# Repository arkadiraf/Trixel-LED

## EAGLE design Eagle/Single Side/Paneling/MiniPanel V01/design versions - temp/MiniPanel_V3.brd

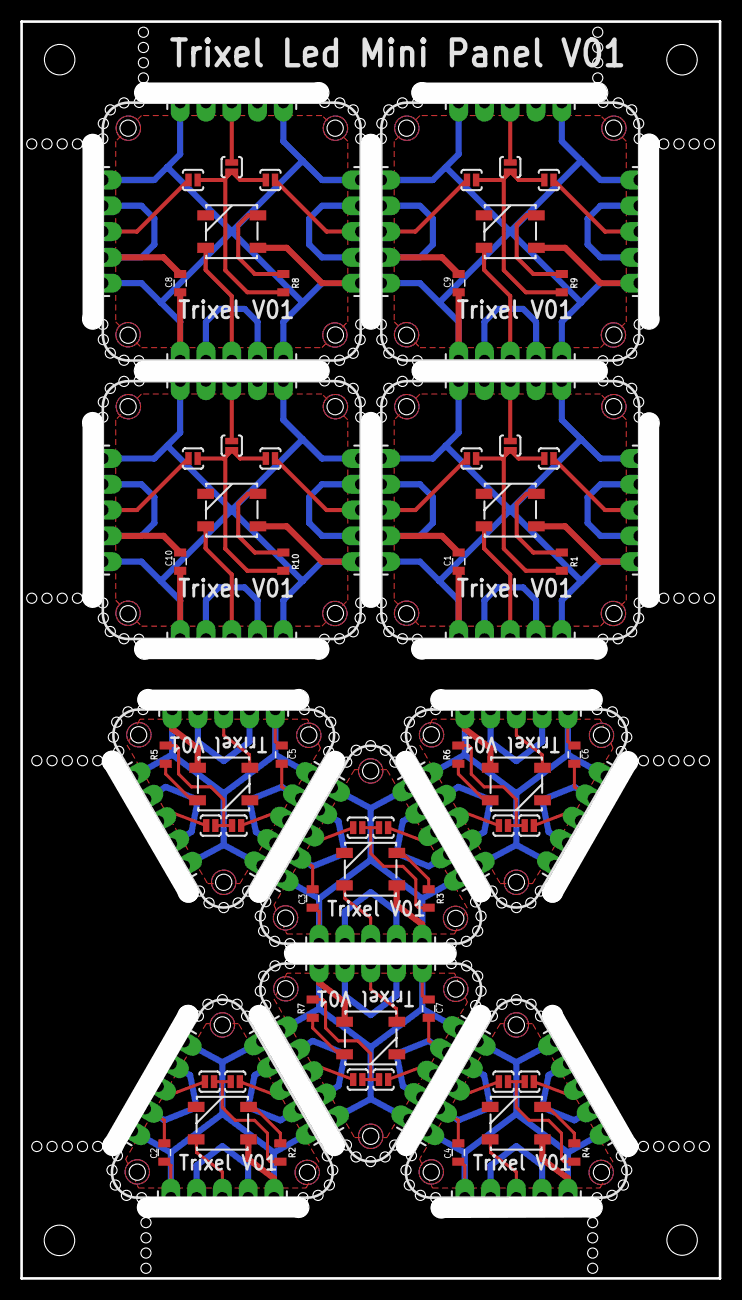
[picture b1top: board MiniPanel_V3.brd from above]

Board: 2 copper layers, 68.8 x 123.8 mm, 88 parts (0 on the bottom side), 74 nets.

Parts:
C1, C2, C3, C4, C5, C6, C7, C8, C9, C10: 0.1uF; 0805
D1, D2, D3, D4, D5, D6, D7, D8, D9, D10: WS2812B
J1, J2, J3, J4, J5, J6, J7, J8, J9, J10, J11, J12, J13, J14, J15, J16, J17, J18, J19, J20, J21, J22, J23, J24, J25, J26, J27, J28, J29, J30, J31, J32, J33, J34: 1X05_LONGPADS
JP1, JP2, JP3, JP4, JP5, JP6, JP7, JP8, JP9, JP10, JP11, JP12, JP13, JP14, JP15, JP16, JP17, JP18, JP19, JP20, JP21, JP22, JP23, JP24: JUMPER-PAD-2-NOYES_SILK; PAD-JUMPER-2-NO_YES_SILK
R1, R8, R9, R10: 0805
R2, R3, R4, R5, R6, R7: 1k; 0805

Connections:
DIN: D1.4, J22.3
DIN1: D2.4, J3.3
DIN2: D3.4, J7.3
DIN3: D4.4, J10.3
DIN4: D5.4, J13.3
DIN5: D6.4, J16.3
DIN6: D7.4, J19.3
DIN7: D8.4, J26.3
DIN8: D9.4, J30.3
DIN9: D10.4, J34.3
DOUT: JP1.1, JP2.1, JP15.1, R1.2
DOUT1: JP3.1, JP4.1, R2.2
DOUT2: JP5.1, JP6.1, R3.2
DOUT3: JP7.1, JP8.1, R4.2
DOUT4: JP9.1, JP10.1, R5.2
DOUT5: JP11.1, JP12.1, R6.2
DOUT6: JP13.1, JP14.1, R7.2
DOUT7: JP16.1, JP17.1, JP18.1, R8.2
DOUT8: JP19.1, JP20.1, JP21.1, R9.2
DOUT9: JP22.1, JP23.1, JP24.1, R10.2
GND: C1.1, D1.3, J1.2, J1.4, J2.2, J2.4, J4.2, J4.4, J22.2, J22.4
GND1: C2.1, D2.3, J3.2, J3.4, J5.2, J5.4, J6.2, J6.4
GND2: C3.1, D3.3, J7.2, J7.4, J8.2, J8.4, J9.2, J9.4
GND3: C4.1, D4.3, J10.2, J10.4, J11.2, J11.4, J12.2, J12.4
GND4: C5.1, D5.3, J13.2, J13.4, J14.2, J14.4, J15.2, J15.4
GND5: C6.1, D6.3, J16.2, J16.4, J17.2, J17.4, J18.2, J18.4
GND6: C7.1, D7.3, J19.2, J19.4, J20.2, J20.4, J21.2, J21.4
GND7: C8.1, D8.3, J23.2, J23.4, J24.2, J24.4, J25.2, J25.4, J26.2, J26.4
GND8: C9.1, D9.3, J27.2, J27.4, J28.2, J28.4, J29.2, J29.4, J30.2, J30.4
GND9: C10.1, D10.3, J31.2, J31.4, J32.2, J32.4, J33.2, J33.4, J34.2, J34.4
unnamed: J4.3, JP2.2
unnamed: J2.3, JP1.2
unnamed: J1.3, JP15.2
unnamed: J5.3, JP4.2
unnamed: D2.2, R2.1
unnamed: J6.3, JP3.2
unnamed: J8.3, JP6.2
unnamed: D3.2, R3.1
unnamed: J9.3, JP5.2
unnamed: J11.3, JP8.2
unnamed: D4.2, R4.1
unnamed: J12.3, JP7.2
unnamed: J14.3, JP10.2
unnamed: D5.2, R5.1
unnamed: J15.3, JP9.2
unnamed: J17.3, JP12.2
unnamed: D6.2, R6.1
unnamed: J18.3, JP11.2
unnamed: J20.3, JP14.2
unnamed: D7.2, R7.1
unnamed: J21.3, JP13.2
unnamed: D1.2, R1.1
unnamed: J25.3, JP17.2
unnamed: J24.3, JP16.2
unnamed: J23.3, JP18.2
unnamed: D8.2, R8.1
unnamed: J29.3, JP20.2
unnamed: J28.3, JP19.2
unnamed: J27.3, JP21.2
unnamed: D9.2, R9.1
unnamed: J33.3, JP23.2
unnamed: J32.3, JP22.2
unnamed: J31.3, JP24.2
unnamed: D10.2, R10.1
VIN: C1.2, D1.1, J1.1, J1.5, J2.1, J2.5, J4.1, J4.5, J22.1, J22.5
VIN1: C2.2, D2.1, J3.1, J3.5, J5.1, J5.5, J6.1, J6.5
VIN2: C3.2, D3.1, J7.1, J7.5, J8.1, J8.5, J9.1, J9.5
VIN3: C4.2, D4.1, J10.1, J10.5, J11.1, J11.5, J12.1, J12.5
VIN4: C5.2, D5.1, J13.1, J13.5, J14.1, J14.5, J15.1, J15.5
VIN5: C6.2, D6.1, J16.1, J16.5, J17.1, J17.5, J18.1, J18.5
VIN6: C7.2, D7.1, J19.1, J19.5, J20.1, J20.5, J21.1, J21.5
VIN7: C8.2, D8.1, J23.1, J23.5, J24.1, J24.5, J25.1, J25.5, J26.1, J26.5
VIN8: C9.2, D9.1, J27.1, J27.5, J28.1, J28.5, J29.1, J29.5, J30.1, J30.5
VIN9: C10.2, D10.1, J31.1, J31.5, J32.1, J32.5, J33.1, J33.5, J34.1, J34.5

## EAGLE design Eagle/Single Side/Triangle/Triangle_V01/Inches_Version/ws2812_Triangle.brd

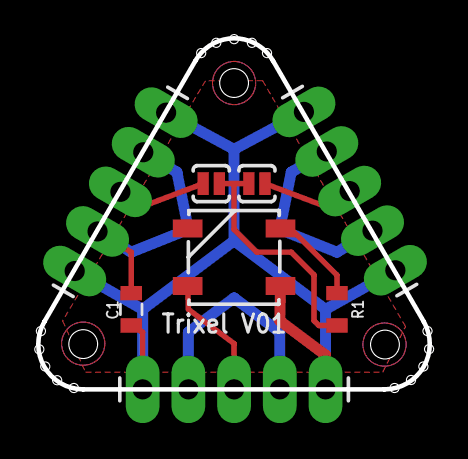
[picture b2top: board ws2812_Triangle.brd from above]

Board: 2 copper layers, 21.7 x 19.5 mm, 8 parts (0 on the bottom side), 7 nets.

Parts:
C1: 0.1uF; 0805
D1: WS2812B
J1, J2, J4: 1X05_LONGPADS
JP1, JP2: JUMPER-PAD-2-NOYES_SILK; PAD-JUMPER-2-NO_YES_SILK
R1: 1k; 0805

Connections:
DIN: D1.4, J4.3
DOUT: JP1.1, JP2.1, R1.2
GND: C1.1, D1.3, J1.2, J1.4, J2.2, J2.4, J4.2, J4.4
unnamed: J1.3, JP2.2
unnamed: J2.3, JP1.2
unnamed: D1.2, R1.1
VIN: C1.2, D1.1, J1.1, J1.5, J2.1, J2.5, J4.1, J4.5

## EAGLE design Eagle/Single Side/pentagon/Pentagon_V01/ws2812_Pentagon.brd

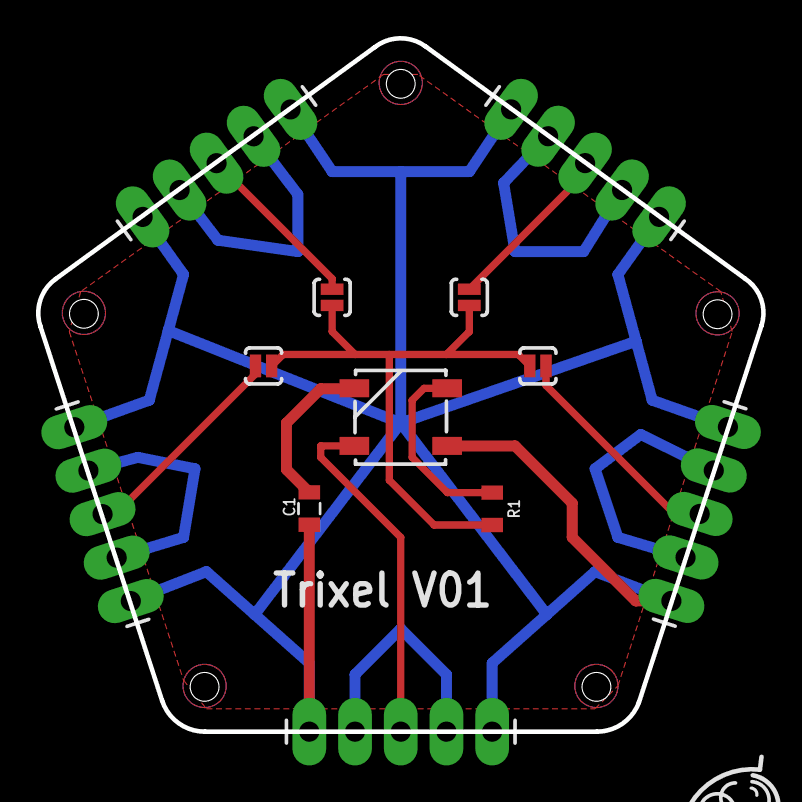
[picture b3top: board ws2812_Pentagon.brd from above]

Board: 2 copper layers, 40.3 x 38.5 mm, 12 parts (0 on the bottom side), 9 nets.

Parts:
C1: 0.1uF; 0805
D1: WS2812B
J6, J7, J8, J9, J10: 1X05_LONGPADS
JP1, JP2, JP3, JP4: JUMPER-PAD-2-NOYES_SILK; PAD-JUMPER-2-NO_YES_SILK
R1: 0805

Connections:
DIN: D1.4, J6.3
DOUT: JP1.1, JP2.1, JP3.1, JP4.1, R1.2
GND: C1.1, D1.3, J6.2, J6.4, J7.2, J7.4, J8.2, J8.4, J9.2, J9.4, J10.2, J10.4
unnamed: J9.3, JP2.2
unnamed: J8.3, JP1.2
unnamed: D1.2, R1.1
unnamed: J7.3, JP4.2
unnamed: J10.3, JP3.2
VIN: C1.2, D1.1, J6.1, J6.5, J7.1, J7.5, J8.1, J8.5, J9.1, J9.5, J10.1, J10.5

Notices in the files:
parts and their libraries:
SparkFun-Capacitors: Licensing: Creative Commons ShareAlike 4.0 International - https://creativecommons.org/licenses/by-sa/4.0
